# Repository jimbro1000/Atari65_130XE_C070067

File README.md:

# Atari 65/130XE Reproduction

## Introduction

This project reproduces the PCB used in the Atari 65XE and 130XE.
There are several variations on the board, this targets the
earlier design that used 8 or 16 4164 DRAM chips. These boards are
marked as C070065 or C070067

The initial primary goal is to support diagnostics rather than
create replacement boards but this will likely become possible as 
the project progresses.

### Sponsorship and Support

A bare donor board has been provided by Lee of "More Fun Making It"
and founder of the Retro Hardware Discord to save my working board 
from being torn down.

PCBWay are sponsoring the initial fabrication of the board by covering
the costs and providing high quality, rapid turnaround prototyping
capabilities.

An honourable mention also goes to Henry of the Retro Hardware Discord
for providing spares to help fix my 65XE (and thus negating the direct 
need for any of the work here)

### Sources

The schematics that the design is taken from are themselves copies
of the original work.

The primary source of information is taken from an updated version
of the Atari workshop manual updated and reproduced by JER/Eightbitter.
A second source comes from earlier reproduction drawings by Jerzy Sobola.

## Interactive Bill of Materials

The initial output of the project will be a web based interactive bill
of materials that includes trace routing. This allows visual 
identification of individual traces on the board and the devices each
trace connects to.

## Engineering Files

Once the accuracy of the reproduction is verified the project output
will include gerber files to facilitate the fabrication of boards.

### Accuracy

While every effort is made to ensure that the board design is accurate
and faithful to the original, there will be variations in tolerances that
result in the need for fettling of the board to correctly fit the
original case.

The board design provided will be a direct copy in terms of the components
used and as such will require original parts, some of which are
effectively unobtainable other than from donor machines - notably the SIO
port, expansion port and half of the custom chips. 

The SALLY CPU chip can be replaced with an adapted 65C02 to add the missing
HALT signal. FREDDIE and POKEY are available as reproductions. The PIA can 
be replaced with a MC68B21 (or equivalent).

## Progress

Revision 1 of the schematics and board design is complete, awaiting fabrication and test. Some tweaks to the schematic have been made to
match the donor board. The factory bodge for the GTIA select line has
been incorporated into the design, this has resulted in some 
alterations to routing but leaves a much tidier board when completed.

## References

FREDDIE replacement - design by Candle'O'Sin. Sold by Retro Lemon in two 
flavours:  
* https://retrolemon.co.uk/atari-8bit-upgrades/182-freddie-cpld.html
* https://retrolemon.co.uk/atari-8bit-upgrades/81-freddie-module.html
  (only for use with matching SRAM module)

SALLY conversion - open source project you can fabricate (or have fabricated 
for you)
* https://github.com/TheByteAttic/Sally-to-W65C02S-adapter
* https://www.pcbway.com/project/shareproject/6502__W65C02S__to_Atari_SALLY_adapter_Board.html

POKEY replacement (and upgrade) - design by Retronics. Sold by Retro Lemon:
* https://retrolemon.co.uk/atari-8bit-upgrades/148-pokeymax.html

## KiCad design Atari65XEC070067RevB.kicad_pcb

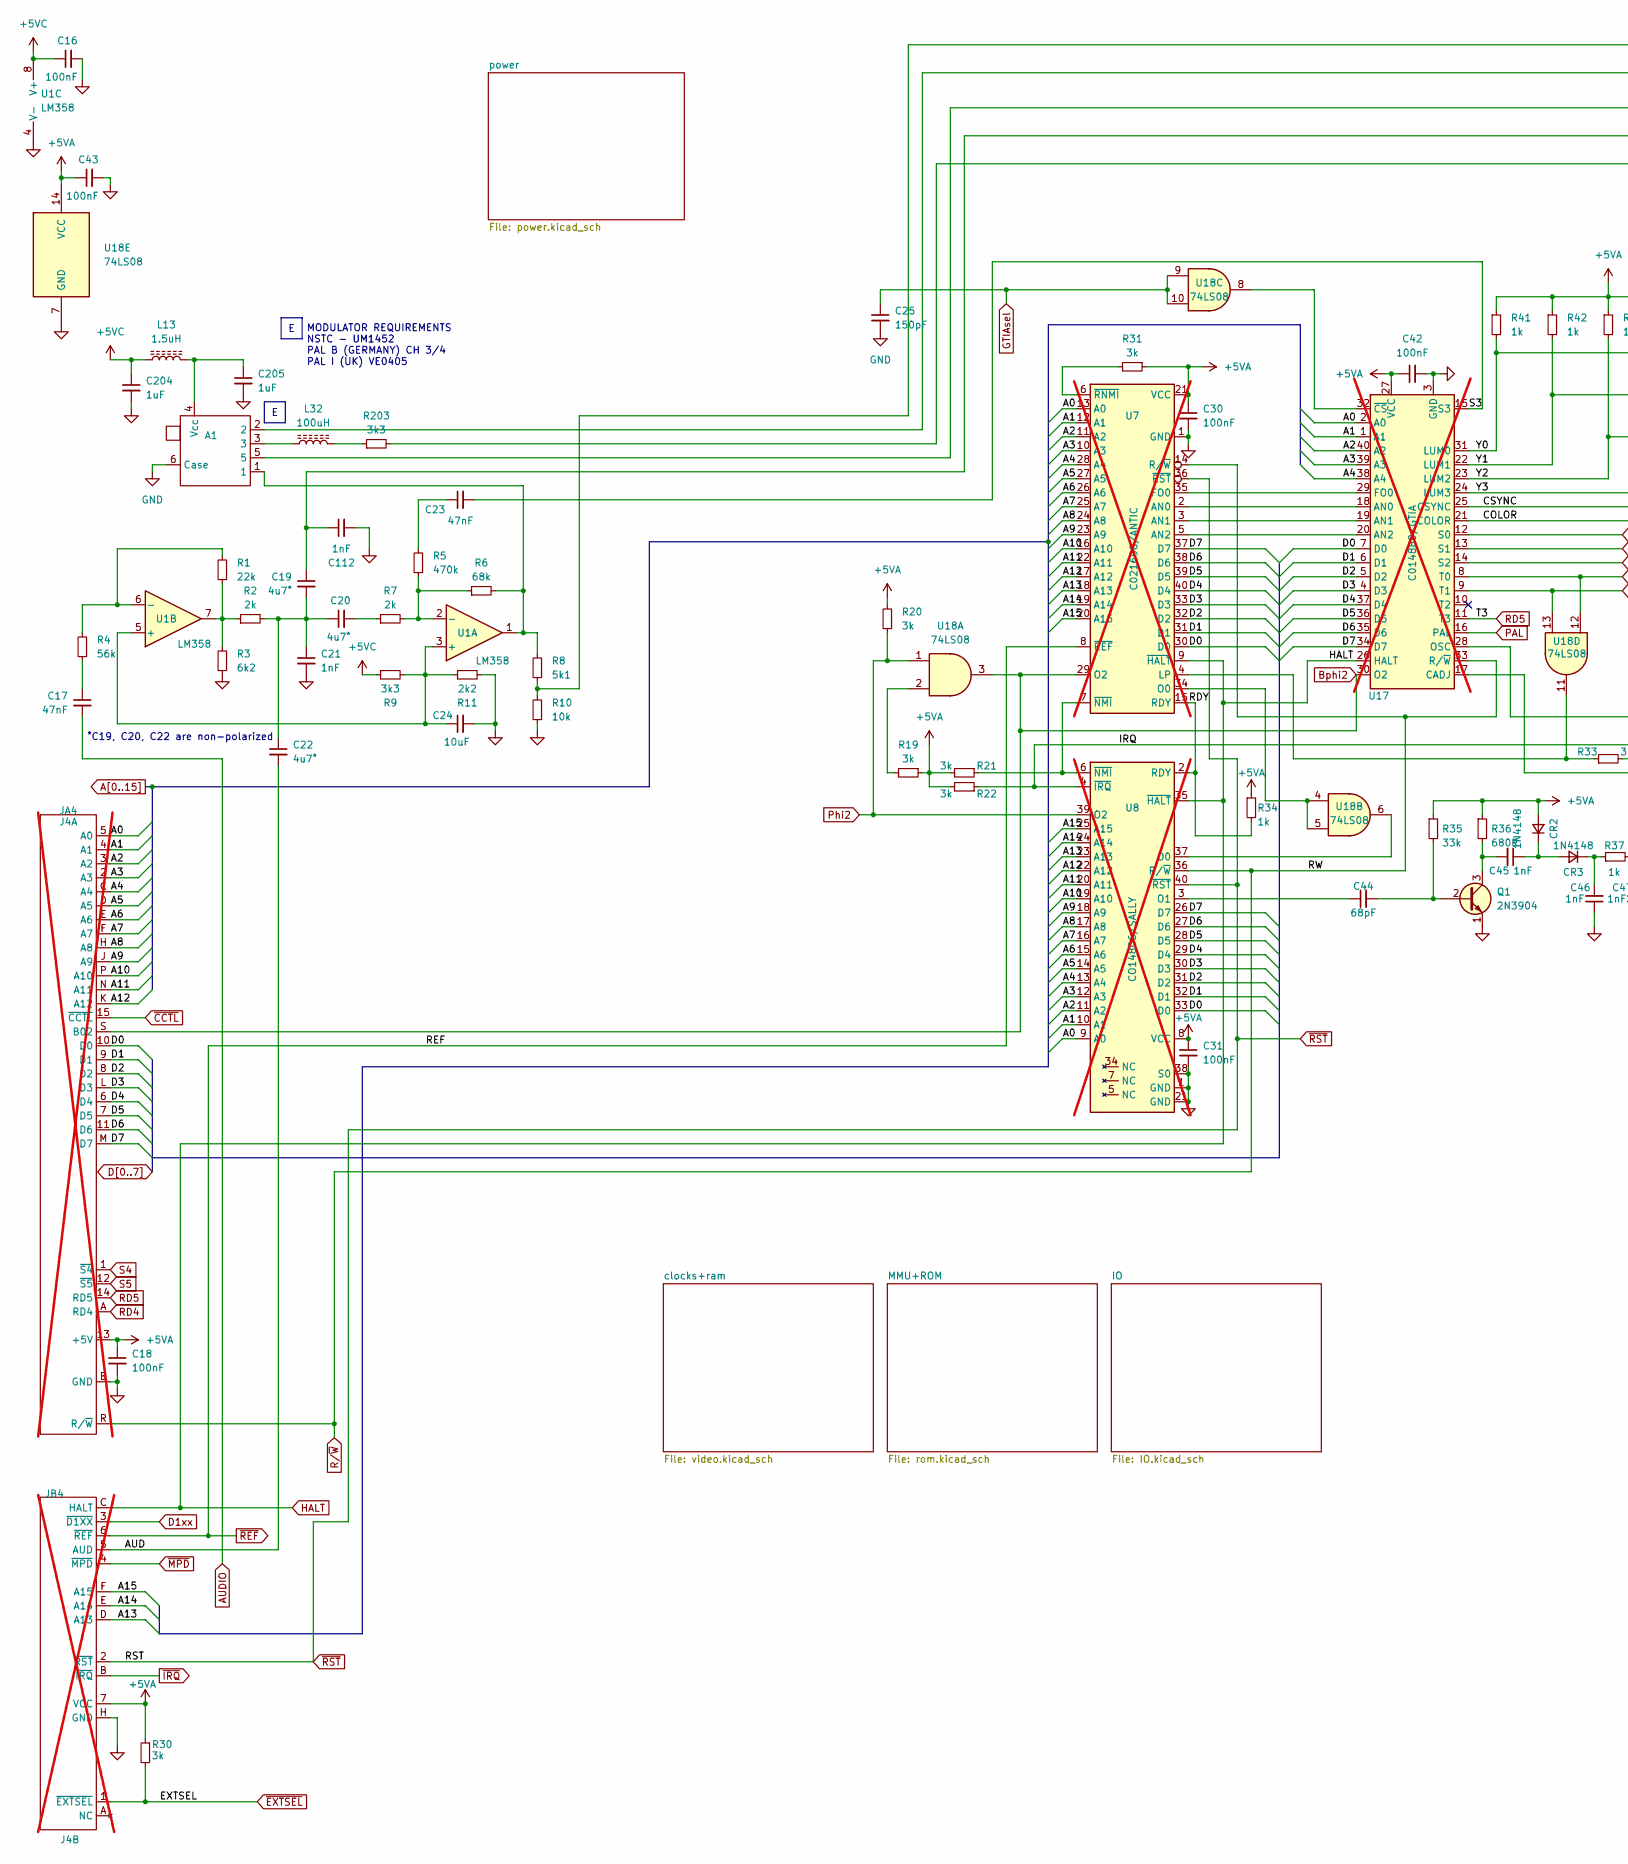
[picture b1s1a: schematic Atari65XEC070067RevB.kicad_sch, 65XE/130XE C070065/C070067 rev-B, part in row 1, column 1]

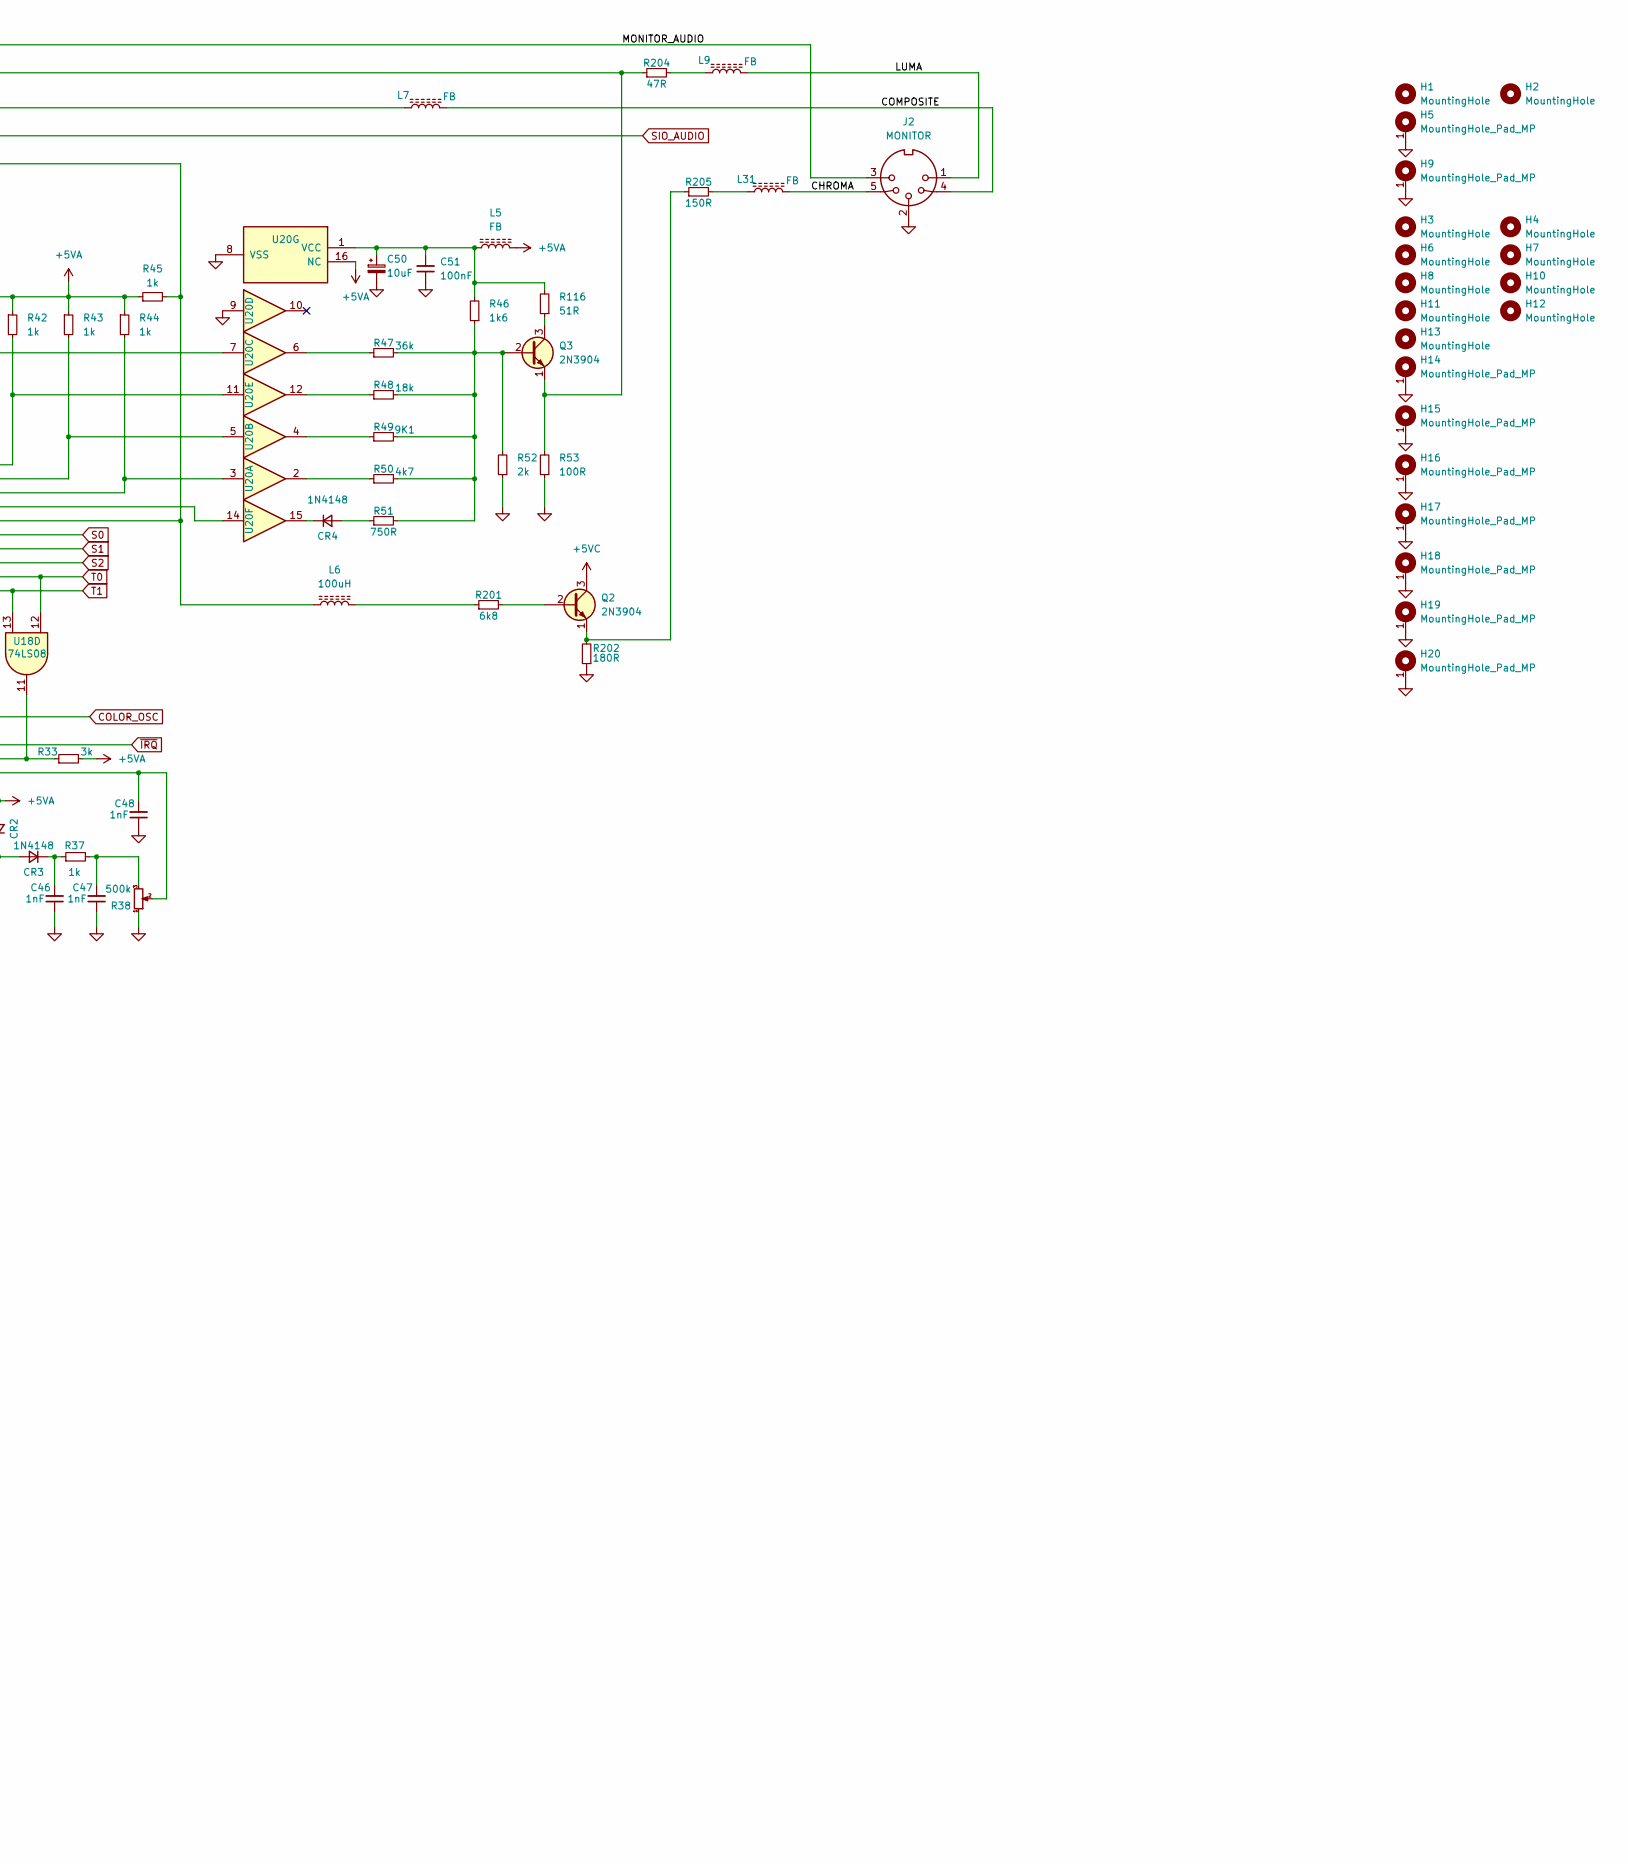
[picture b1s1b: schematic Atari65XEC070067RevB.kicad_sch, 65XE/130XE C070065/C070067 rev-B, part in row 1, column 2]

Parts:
A1: RF_Modulator_MDG-UB360S
C16, C18, C30, C31, C42, C43, C51: 100nF; C_Axial_L5.1mm_D2.7mm_P12.72mm_Horizontal; DigiKey 1109PHCT-ND
C17, C23: 47nF; C_Axial_L5.1mm_D2.7mm_P12.72mm_Horizontal; DigiKey 1107PHCT-ND
C19, C20, C22: 4u7^{*}; CE_NP_Radial_D8.0mm_P2.50mm; DigiKey 475BPS100M-ND
C21, C45, C46, C47, C48, C112: 1nF; C_Axial_L5.1mm_D2.7mm_P12.72mm_Horizontal; DigiKey 1216PHCT-ND
C24: 10uF; CP_Axial_L10.0mm_D4.5mm_P15.00mm_Horizontal; DigiKey 1572-1035-1-ND
C25: 150pF; C_Axial_L5.1mm_D2.7mm_P12.72mm_Horizontal; DigiKey 399-4456-1-ND
C44: 68pF; C_Axial_L5.1mm_D2.7mm_P12.72mm_Horizontal; DigiKey 1018PHCT-ND
C50: 10uF; CP_Radial_D5.0mm_P2.50mm; DigiKey 399-18269-1-ND
C204, C205: 1uF; C_Axial_L5.1mm_D2.7mm_P12.72mm_Horizontal; DigiKey 399-C410C105K5R5TA7200CT-ND
CR2, CR3, CR4: 1N4148; D_DO-35_SOD27_P12.70mm_Horizontal; DigiKey 1N4148FS-ND
H1, H2: MountingHole; Cutout
H3, H4, H6, H7, H8, H10, H11, H12, H13: MountingHole; MountingHole_3.2mm_M3_DIN965
H5, H9: MountingHole_Pad_MP; MountingHole_4.3mm_M4_ISO7380_Pad_TopBottom
H14, H15, H16, H17, H18, H19, H20: MountingHole_Pad_MP; Untitled
J2: MONITOR; CUI_SDS-50J; DigiKey CP-2350-ND
JA4: J4A; CARTRIDGE; not fitted
JB4: J4B; EXPANSION; not fitted
L5, L7, L9, L31: FB; L_Axial_L7.0mm_D3.3mm_P12.70mm_Horizontal_Fastron_MICC; DigiKey 1934-1417-1-ND
L6, L32: 100uH; L_Axial_L7.0mm_D3.3mm_P12.70mm_Horizontal_Fastron_MICC; DigiKey 118-78F101J-TR-RCCT-ND
L13: 1.5uH; L_Axial_L7.0mm_D3.3mm_P12.70mm_Horizontal_Fastron_MICC; DigiKey 78F1R5K-RC-ND
Q1, Q2, Q3: 2N3904; TO-92L_Inline_Wide; DigiKey 4878-2N3904CT-ND
R1: 22k; R_Axial_L9.0mm_D2.7mm_P12.70mm_Horizontal; DigiKey CF14JT22K0CT-ND
R2, R7, R52: 2k; R_Axial_L9.0mm_D2.7mm_P12.70mm_Horizontal; DigiKey CF14JT2K00CT-ND
R3: 6k2; R_Axial_L9.0mm_D2.7mm_P12.70mm_Horizontal; DigiKey CF14JT6K20CT-ND
R4: 56k; R_Axial_L9.0mm_D2.7mm_P12.70mm_Horizontal; DigiKey CF14JT56K0CT-ND
R5: 470k; R_Axial_L9.0mm_D2.7mm_P12.70mm_Horizontal; DigiKey S470KQCT-ND
R6: 68k; R_Axial_L9.0mm_D2.7mm_P12.70mm_Horizontal; DigiKey CF14JT68K0CT-ND
R8: 5k1; R_Axial_L9.0mm_D2.7mm_P12.70mm_Horizontal; DigiKey CF14JT5K10CT-ND
R9, R203: 3k3; R_Axial_L9.0mm_D2.7mm_P12.70mm_Horizontal; DigiKey CF14JT3K30CT-ND
R10: 10k; R_Axial_L9.0mm_D2.7mm_P12.70mm_Horizontal; DigiKey CF14JT10K0CT-ND
R11: 2k2; R_Axial_L9.0mm_D2.7mm_P12.70mm_Horizontal; DigiKey CF14JT2K20CT-ND
R19, R20, R21, R22, R30, R31, R33: 3k; R_Axial_L9.0mm_D2.7mm_P12.70mm_Horizontal; DigiKey CF14JT3K00CT-ND
R34, R37, R41, R42, R43, R44, R45: 1k; R_Axial_L9.0mm_D2.7mm_P12.70mm_Horizontal; DigiKey CF14JT1K00CT-ND
R35: 33k; R_Axial_L9.0mm_D2.7mm_P12.70mm_Horizontal; DigiKey CF14JT33K0CT-ND
R36: 680R; R_Axial_L9.0mm_D2.7mm_P12.70mm_Horizontal; DigiKey CF14JT680RCT-ND
R38: 500k; Potentiometer_Bourns_3352E_Vertical; DigiKey 3352E-504LF-ND
R46: 1k6; R_Axial_L9.0mm_D2.7mm_P12.70mm_Horizontal; DigiKey CF14JT1K60CT-ND
R47: 36k; R_Axial_L9.0mm_D2.7mm_P12.70mm_Horizontal; DigiKey CF14JT36K0CT-ND
R48: 18k; R_Axial_L9.0mm_D2.7mm_P12.70mm_Horizontal; DigiKey CF14JT18K0CT-ND
R49: 9K1; R_Axial_L9.0mm_D2.7mm_P12.70mm_Horizontal; DigiKey CF14JT9K10CT-ND
R50: 4k7; R_Axial_L9.0mm_D2.7mm_P12.70mm_Horizontal; DigiKey CF14JT4K70CT-ND
R51: 750R; R_Axial_L9.0mm_D2.7mm_P12.70mm_Horizontal; DigiKey CF14JT750RCT-ND
R53: 100R; R_Axial_L9.0mm_D2.7mm_P12.70mm_Horizontal; DigiKey CF14JT100RCT-ND
R116: 51R; R_Axial_L9.0mm_D2.7mm_P12.70mm_Horizontal; DigiKey CF14JT51R0CT-ND
R201: 6k8; R_Axial_L9.0mm_D2.7mm_P12.70mm_Horizontal; DigiKey CF14JT6K80CT-ND
R202: 180R; R_Axial_L9.0mm_D2.7mm_P12.70mm_Horizontal; DigiKey CF14JT180RCT-ND
R204: 47R; R_Axial_L9.0mm_D2.7mm_P12.70mm_Horizontal; DigiKey CF14JT47R0CT-ND
R205: 150R; R_Axial_L9.0mm_D2.7mm_P12.70mm_Horizontal; DigiKey CF14JT150RCT-ND
U1: LM358; DIP-8_W7.62mm; DigiKey 296-1395-5-ND
U7: C021698/ANTIC; DIP-40_W15.24mm; not fitted
U8: CO14806/SALLY; DIP-40_W15.24mm; not fitted
U17: C014889/GTIA; DIP-40_W15.24mm; not fitted
U18: 74LS08; DIP-14_W7.62mm; DigiKey 296-1633-5-ND
U20: 4050; DIP-16_W7.62mm; DigiKey 296-2056-ND

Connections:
+5VA: C18.1, C30.1, C31.1, C42.1, C43.1, CR2.2 (A), JA4.13 (+5V), JB4.7 (VCC), L5.2, R19.1, R20.2, R21.2, R22.2, R30.1, R31.1, R33.2, R34.1, R35.1, R36.1, R41.1, R42.1, R43.1, R44.1, R45.1, U7.21 (VCC), U8.8 (VCC), U17.27 (VCC), U18.14 (VCC), U20.16 (NC); also elsewhere on the board
+5VC: C16.1, C204.1, L13.1, Q2.3 (C), R9.1, U1.8 (V+); also elsewhere on the board
/AUD: C22.2, JB4.5 (AUD)
/CHROMA: J2.5, L31.2
/COLOR: L6.1, R45.2, R203.2, U17.21 (COLOR)
/COMPOSITE: J2.4, L7.2
/CSYNC: U17.25 (CSYNC), U20.14
/LUMA: J2.1, L9.2
/MONITOR_AUDIO: J2.3, R8.1, R10.2
/RDY: R34.2, U7.15 (RDY), U8.2 (RDY)
/S3: C23.2, U17.15 (S3)
/Y0: R41.2, U17.31 (LUM0), U20.7
/Y1: R42.2, U17.22 (LUM1), U20.11
/Y2: R43.2, U17.23 (LUM2), U20.5
/Y3: R44.2, U17.24 (LUM3), U20.3
A0: JA4.5 (A0), U7.13 (A0), U8.9 (A0), U17.2 (A0); also elsewhere on the board
A1: JA4.4 (A1), U7.12 (A1), U8.10 (A1), U17.1 (A1); also elsewhere on the board
A2: JA4.3 (A2), U7.11 (A2), U8.11 (A2), U17.40 (A2); also elsewhere on the board
A3: JA4.2 (A3), U7.10 (A3), U8.12 (A3), U17.39 (A3); also elsewhere on the board
A4: JA4.C (A4), U7.28 (A4), U8.13 (A4), U17.38 (A4); also elsewhere on the board
A5: JA4.D (A5), U7.27 (A5), U8.14 (A5); also elsewhere on the board
A6: JA4.E (A6), U7.26 (A6), U8.15 (A6); also elsewhere on the board
A7: JA4.F (A7), U7.25 (A7), U8.16 (A7); also elsewhere on the board
A8: JA4.H (A8), U7.24 (A8), U8.17 (A8); also elsewhere on the board
A9: JA4.J (A9), U7.23 (A9), U8.18 (A9); also elsewhere on the board
A10: JA4.P (A10), U7.16 (A10), U8.19 (A10); also elsewhere on the board
A11: JA4.N (A11), U7.22 (A11), U8.20 (A11); also elsewhere on the board
A12: JA4.K (A12), U7.17 (A12), U8.22 (A12); also elsewhere on the board
A13: JB4.D (A13), U7.18 (A13), U8.23 (A13); also elsewhere on the board
A14: JB4.E (A14), U7.19 (A14), U8.24 (A14); also elsewhere on the board
A15: JB4.F (A15), U7.20 (A15), U8.25 (A15); also elsewhere on the board
AUDIO: C17.2; also elsewhere on the board
Bphi2: JA4.S (B02), U7.29 (O2), U17.30 (O2), U18.3; also elsewhere on the board
COLOR_OSC: U17.28 (OSC); also elsewhere on the board
D0: JA4.10 (D0), U7.30 (D0), U8.33 (D0), U17.7 (D0); also elsewhere on the board
D1: JA4.9 (D1), U7.31 (D1), U8.32 (D1), U17.6 (D1); also elsewhere on the board
D1xx: JB4.3 (~D1XX); also elsewhere on the board
D2: JA4.8 (D2), U7.32 (D2), U8.31 (D2), U17.5 (D2); also elsewhere on the board
D3: JA4.L (D3), U7.33 (D3), U8.30 (D3), U17.4 (D3); also elsewhere on the board
D4: JA4.6 (D4), U7.40 (D4), U8.29 (D4), U17.37 (D4); also elsewhere on the board
D5: JA4.7 (D5), U7.39 (D5), U8.28 (D5), U17.36 (D5); also elsewhere on the board
D6: JA4.11 (D6), U7.38 (D6), U8.27 (D6), U17.35 (D6); also elsewhere on the board
D7: JA4.M (D7), U7.37 (D7), U8.26 (D7), U17.34 (D7); also elsewhere on the board
GND: A1.6 (Case), C16.2, C18.2, C21.2, C24.2, C25.2, C30.2, C31.2, C42.2, C43.2, C46.1, C47.1, C48.1, C50.2, C51.1, C112.2, C204.2, C205.2, H5.1, H9.1, H14.1, H15.1, H16.1, H17.1, H18.1, H19.1, H20.1, J2.2, JA4.B (GND), JB4.H (GND), Q1.1 (E), R3.1, R10.1, R11.2, R38.1, R52.1, R53.1, R202.1, U1.4 (V-), U7.1 (GND), U8.1 (GND), U8.21 (GND), U8.38 (S0), U17.3 (GND), U18.7 (GND), U20.8 (VSS), U20.9; also elsewhere on the board
GTIAsel: C25.1, U18.9, U18.10; also elsewhere on the board
HALT: JB4.C (HALT), U7.9 (~HALT), U8.35 (~HALT), U17.26 (HALT); also elsewhere on the board
unnamed: A1.1, R6.2, R8.2, U1.1
unnamed: A1.3, L32.1
unnamed: A1.5, L7.1
unnamed: A1.4 (Vcc), C205.1, L13.2
unnamed: C17.1, R4.1
unnamed: C19.2, C20.1, C21.1, C22.1, R2.2
unnamed: C20.2, R7.1
unnamed: C23.1, R5.2
unnamed: C47.2, R37.2, R38.3
unnamed: C45.1, CR2.1 (K), CR3.2 (A)
unnamed: C46.2, CR3.1 (K), R37.1
unnamed: CR4.2 (A), R51.1
unnamed: CR4.1 (K), U20.15
unnamed: L6.2, R201.1
unnamed: L9.1, R204.2
unnamed: L31.1, R205.2
unnamed: L32.2, R203.1
unnamed: C44.2, Q1.2 (B), R35.2
unnamed: C45.2, Q1.3 (C), R36.2
unnamed: Q2.2 (B), R201.2
unnamed: Q2.1 (E), R202.2, R205.1
unnamed: Q3.2 (B), R46.1, R47.2, R48.2, R49.2, R50.2, R51.2, R52.2
unnamed: Q3.3 (C), R116.1
unnamed: A1.2, Q3.1 (E), R53.2, R204.1
unnamed: R1.1, R2.1, R3.2, U1.7
unnamed: R19.2, U18.2
unnamed: R47.1, U20.6
unnamed: R48.1, U20.12
unnamed: R49.1, U20.4
unnamed: R50.1, U20.2
unnamed: C24.1, R9.2, R11.1, U1.3 (+), U1.5 (+)
unnamed: R5.1, R6.1, R7.2, U1.2 (-)
unnamed: R1.2, R4.2, U1.6 (-)
unnamed: R33.1, U7.4 (LP), U18.11
unnamed: U7.34 (O0), U18.4, U18.5
unnamed: R21.1, U7.7 (~NMI), U8.6 (~NMI)
unnamed: R31.2, U7.6 (~RNMI)
unnamed: U8.37 (O0), U18.6
unnamed: C44.1, U8.3 (O1)
unnamed: U7.2 (AN0), U17.18 (AN0)
unnamed: U7.3 (AN1), U17.19 (AN1)
unnamed: U7.5 (AN2), U17.20 (AN2)
unnamed: C48.2, R38.2, U17.17 (CADJ)
unnamed: U7.35 (FO0), U17.29 (FO0)
unnamed: U17.32 (~CS), U18.8
unnamed: C50.1, C51.2, L5.1, R46.2, R116.2, U20.1 (VCC)
PAL: U17.16 (PAL); also elsewhere on the board
Phi2: R20.1, U8.39 (O2), U18.1; also elsewhere on the board
RD4: JA4.A (RD4); also elsewhere on the board
RD5: JA4.14 (RD5), U17.11 (T3); also elsewhere on the board
R/~W: JA4.R (R/~W), U7.14 (R/~W), U8.36 (R/~W), U17.33 (R/~W); also elsewhere on the board
S0: U17.12 (S0); also elsewhere on the board
S1: U17.13 (S1); also elsewhere on the board
S2: U17.14 (S2); also elsewhere on the board
S4: JA4.1 (~S4); also elsewhere on the board
S5: JA4.12 (~S5); also elsewhere on the board
SIO_AUDIO: C19.1, C112.1; also elsewhere on the board
T0: U17.8 (T0), U18.12; also elsewhere on the board
T1: U17.9 (T1), U18.13; also elsewhere on the board
~CCTL: JA4.15 (~CCTL); also elsewhere on the board
~EXTSEL: JB4.1 (~EXTSEL), R30.2; also elsewhere on the board
~IRQ: JB4.B (~IRQ), R22.1, U8.4 (~IRQ); also elsewhere on the board
~MPD: JB4.4 (~MPD); also elsewhere on the board
~REF: JB4.6 (~REF), U7.8 (~REF); also elsewhere on the board
~RST: JB4.2 (~RST), U7.36 (~RST), U8.40 (~RST); also elsewhere on the board

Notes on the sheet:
MODULATOR REQUIREMENTS NSTC - UM1452 PAL B (GERMANY) CH 3/4 PAL I (UK) VE0405
^{*}C19, C20, C22 are non-polarized

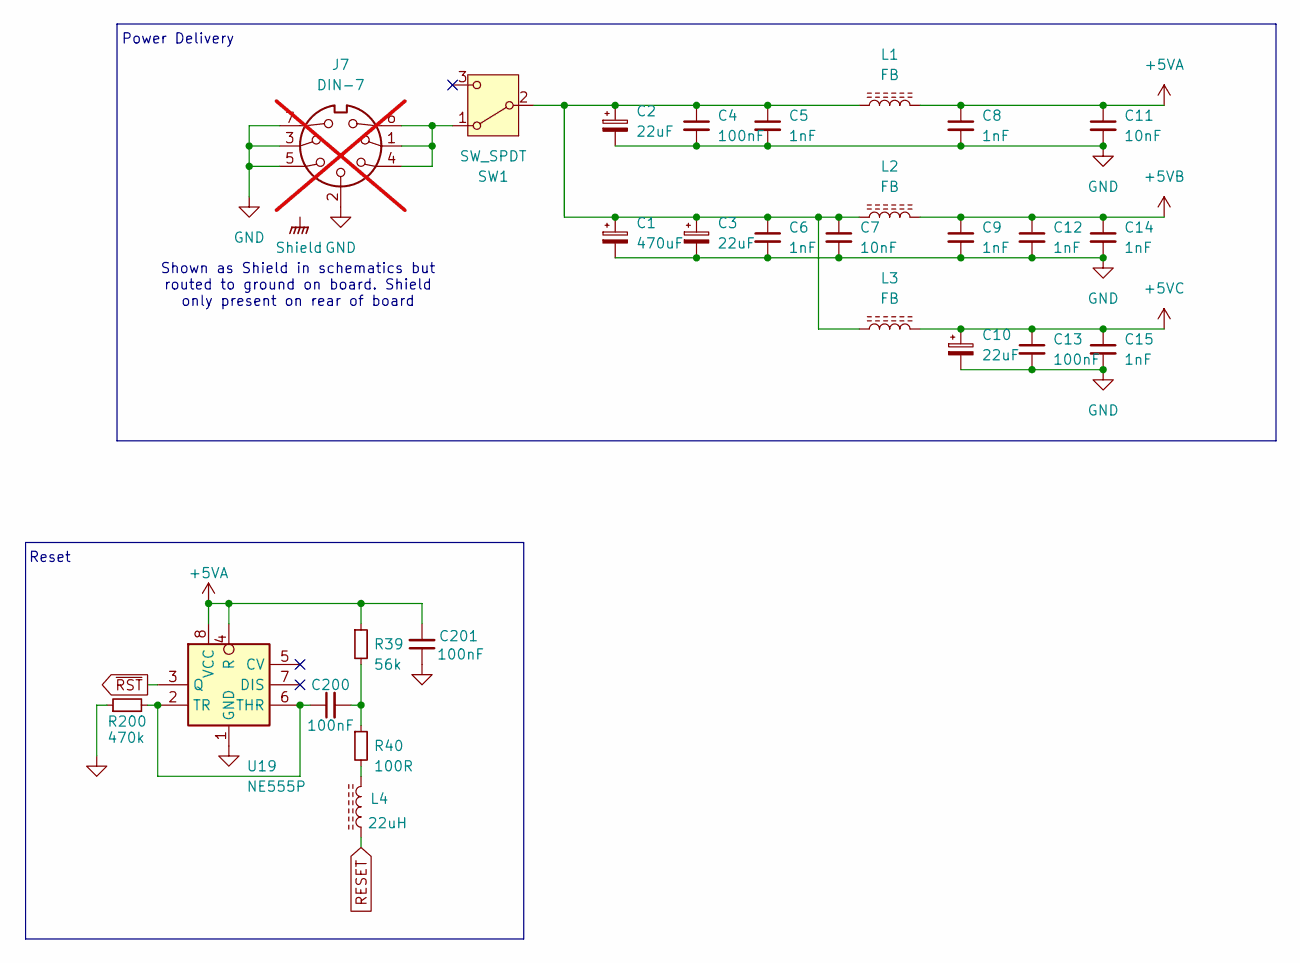
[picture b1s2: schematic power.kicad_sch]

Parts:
C1: 470uF; CP_Radial_D10.0mm_P5.00mm; DigiKey 732-9156-1-ND
C2, C3, C10: 22uF; CP_Axial_L11.0mm_D5.0mm_P18.00mm_Horizontal; DigiKey 1572-1393-ND
C4, C13, C200, C201: 100nF; C_Axial_L5.1mm_D2.7mm_P12.72mm_Horizontal; DigiKey 1109PHCT-ND
C5, C6, C8, C9, C12, C14, C15: 1nF; C_Axial_L5.1mm_D2.7mm_P12.72mm_Horizontal; DigiKey 1216PHCT-ND
C7, C11: 10nF; C_Axial_L5.1mm_D2.7mm_P12.72mm_Horizontal; DigiKey 1103PHCT-ND
J7: DIN-7; CUI_SDS-70J_Atari; not fitted
L1, L2, L3: FB; R_Axial_L9.0mm_D2.7mm_P12.70mm_Horizontal; DigiKey 1934-1417-1-ND
L4: 22uH; L_Axial_L7.0mm_D3.3mm_P12.70mm_Horizontal_Fastron_MICC; DigiKey 541-IRF24ER220JCT-ND
R39: 56k; R_Axial_L9.0mm_D2.7mm_P12.70mm_Horizontal; DigiKey CF14JT56K0CT-ND
R40: 100R; R_Axial_L9.0mm_D2.7mm_P12.70mm_Horizontal; DigiKey CF14JT100RCT-ND
R200: 470k; R_Axial_L9.0mm_D2.7mm_P12.70mm_Horizontal; DigiKey S470KQCT-ND
SW1: SW_SPDT; PowerSwitch
U19: NE555P; DIP-8_W7.62mm; DigiKey 296-NE555P-ND

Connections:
+5VA: C8.1, C11.1, C201.2, L1.2, R39.1, U19.4 (R), U19.8 (VCC); also elsewhere on the board
+5VB: C9.1, C12.1, C14.1, L2.2; also elsewhere on the board
+5VC: C10.1, C13.1, C15.1, L3.2; also elsewhere on the board
GND: C1.2, C2.2, C3.2, C4.2, C5.2, C6.2, C7.2, C8.2, C9.2, C10.2, C11.2, C12.2, C13.2, C14.2, C15.2, C201.1, J7.2, J7.3, J7.5, J7.7, R200.1, U19.1 (GND); also elsewhere on the board
unnamed: C200.2, R39.2, R40.1
unnamed: L4.2, R40.2
unnamed: J7.1, J7.4, J7.6, SW1.1 (A)
unnamed: C1.1, C2.1, C3.1, C4.1, C5.1, C6.1, C7.1, L1.1, L2.1, L3.1, SW1.2 (B)
unnamed: C200.1, R200.2, U19.2 (TR), U19.6 (THR)
RESET: L4.1; also elsewhere on the board
~RST: U19.3 (Q); also elsewhere on the board

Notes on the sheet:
Power Delivery
Shown as Shield in schematics but routed to ground on board. Shield only present on rear of board
Reset
